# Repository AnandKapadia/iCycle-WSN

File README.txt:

README: 

This repository contains all of the files and documentation for the iCycle project. 

00_Documentation
01_Hardware 
	01_00_Reference
		Sparkfun library for the ATmega128RFA1_Dev (https://github.com/sparkfun/ATmega128RFA1_Dev)
	01_01_Library
	01_02_PCB
		v0.1 with arduinio mini, not finished, needs 4 layers
		v0.2 completed board with xbee, buzzer, leds
02_Software 
	01_00_Reference
		Sparkfun library for the ATmega128RFA1_Dev (https://github.com/sparkfun/ATmega128RFA1_Dev)

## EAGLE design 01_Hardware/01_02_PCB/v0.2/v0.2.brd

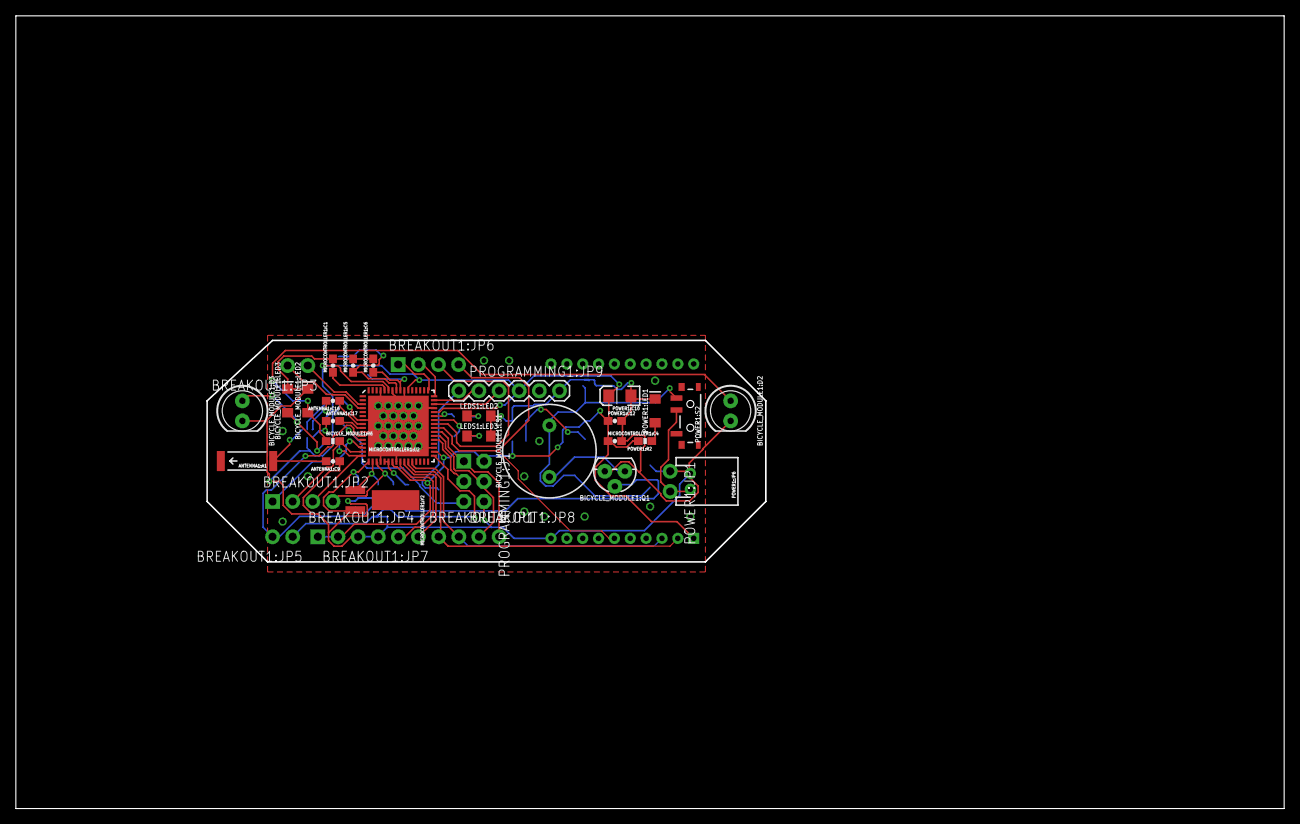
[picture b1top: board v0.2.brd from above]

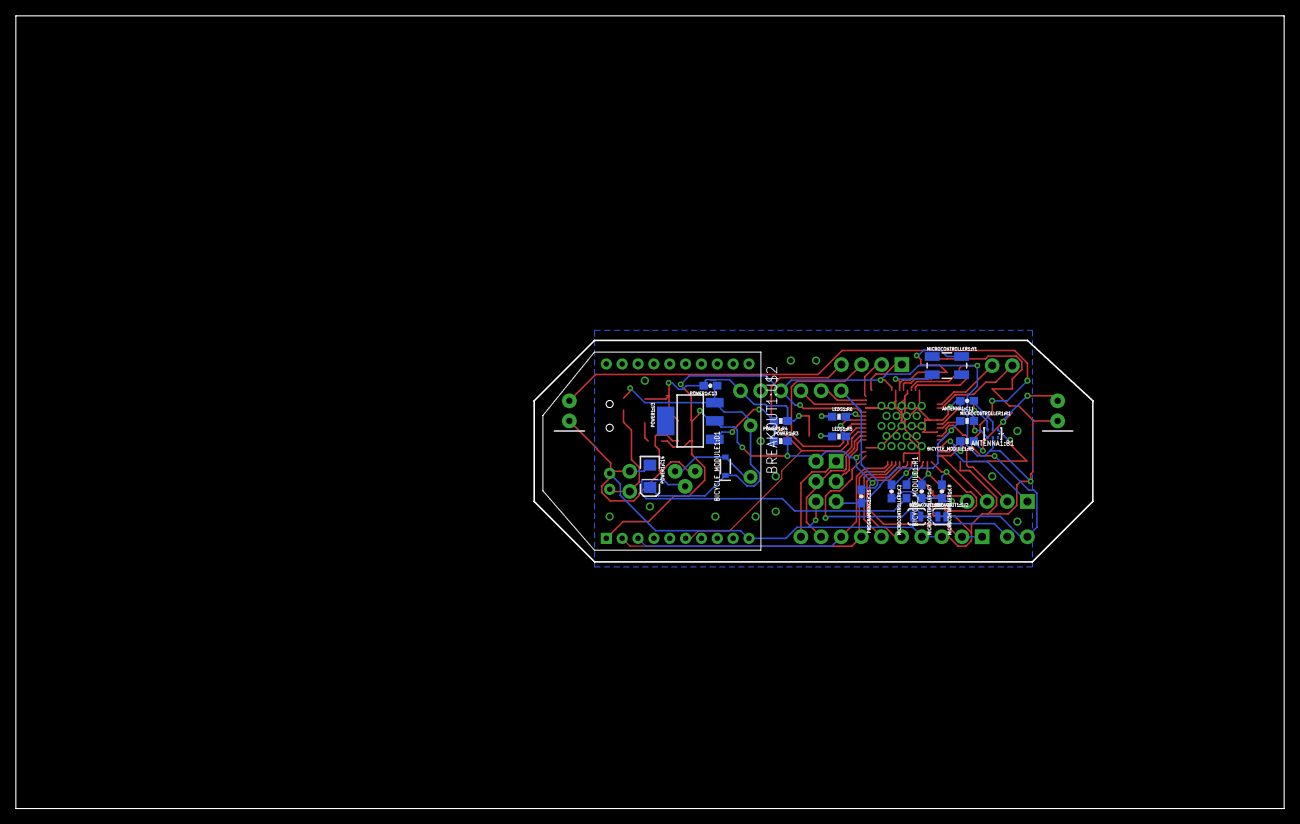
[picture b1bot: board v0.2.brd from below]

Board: 2 copper layers, 160.0 x 100.0 mm, 57 parts (21 on the bottom side), 49 nets.

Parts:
ANTENNA1:A1: ANTENNA2SMD5; ANTENNA-CHIP5
ANTENNA1:B1: 748421245; BALUN-0805
ANTENNA1:C9: 0.75pF; 0603-CAP
ANTENNA1:C11: 22pF; 0603-CAP
ANTENNA1:C16, ANTENNA1:C17: JUMP; 0603-CAP
BICYCLE_MODULE1:D1: 250mA/100V; SOD-323
BICYCLE_MODULE1:D2, BICYCLE_MODULE1:D3: LED_5MM
BICYCLE_MODULE1:LED2, BICYCLE_MODULE1:LED3: GREEN; LED-1206
BICYCLE_MODULE1:LS1: BUZZER-PTH; BUZZER-12MM
BICYCLE_MODULE1:Q1: 600mA/40V; TO-92
BICYCLE_MODULE1:R1: 180; 0603
BICYCLE_MODULE1:R5, BICYCLE_MODULE1:R6: 330; 0603-RES
BREAKOUT1:JP1, BREAKOUT1:JP3, BREAKOUT1:JP5, BREAKOUT1:JP7, BREAKOUT1:JP8: 1X02_NO_SILK
BREAKOUT1:JP2, BREAKOUT1:JP4, BREAKOUT1:JP6: 1X04_NO_SILK
BREAKOUT1:SJ1, BREAKOUT1:SJ2: SJ_2S-TRACE
BREAKOUT1:U$2: XBEE
LEDS1:LED2, LEDS1:LED3: GREEN; LED-1206
LEDS1:R5, LEDS1:R6: 330; 0603-RES
MICROCONTROLLER1:C1, MICROCONTROLLER1:C2, MICROCONTROLLER1:C4: 1uF; 0603-CAP
MICROCONTROLLER1:C5, MICROCONTROLLER1:C6, MICROCONTROLLER1:C7, MICROCONTROLLER1:C8: 12pF; 0603-CAP
MICROCONTROLLER1:R1: 10k; 0603-RES
MICROCONTROLLER1:U2: ATMEGA128RFA1; QFN-64
MICROCONTROLLER1:Y1: 16MHz; CRYSTAL-SMD-5X3
MICROCONTROLLER1:Y2: 32.768kHz; CRYSTAL-32KHZ-SMD
POWER1:C10, POWER1:C14: 10uF; EIA3216
POWER1:C12: 1uF; 0603-CAP
POWER1:C13: 0.1uF; 0603-CAP
POWER1:JP1: 1X02_NO_SILK
POWER1:JP6: JST-2-PTH
POWER1:LED1: RED; LED-1206
POWER1:R2: 1k; 0603-RES
POWER1:R3: 240; 0603-RES
POWER1:R4: 390; 0603-RES
POWER1:S2: SWITCH-SPST-SMD-A
POWER1:U3: LM1117; SOT223
PROGRAMMING1:C15: 0.1uF; 0603-CAP
PROGRAMMING1:J1: ISP; 2X3-NS
PROGRAMMING1:JP9: FTDI; FTDI_BASIC

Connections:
3.3V: BREAKOUT1:JP4.1, BREAKOUT1:JP4.2, BREAKOUT1:U$2.1, MICROCONTROLLER1:C4.1, MICROCONTROLLER1:R1.2, MICROCONTROLLER1:U2.23, MICROCONTROLLER1:U2.34, MICROCONTROLLER1:U2.44, MICROCONTROLLER1:U2.54, MICROCONTROLLER1:U2.59, POWER1:C10.A, POWER1:C12.1, POWER1:R2.2, POWER1:R3.2, POWER1:U3.2, PROGRAMMING1:J1.2, PROGRAMMING1:JP9.VCC
A4: BREAKOUT1:JP3.1, MICROCONTROLLER1:U2.3
A5: BREAKOUT1:JP3.2, MICROCONTROLLER1:U2.4
ANTENNA1:N$62: ANTENNA1:B1.2, ANTENNA1:C11.1
ANTENNA1:N$63: ANTENNA1:B1.3, ANTENNA1:C16.2
ANTENNA1:N$64: ANTENNA1:B1.4, ANTENNA1:C17.1
ANTENNA1:RFANT: ANTENNA1:A1.FEED, ANTENNA1:B1.1, ANTENNA1:C9.2
AVDD: MICROCONTROLLER1:C1.1, MICROCONTROLLER1:U2.60
BICYCLE_MODULE1:N$1: BICYCLE_MODULE1:Q1.2, BICYCLE_MODULE1:R1.2
BICYCLE_MODULE1:N$2: BICYCLE_MODULE1:D1.A, BICYCLE_MODULE1:LS1.-, BICYCLE_MODULE1:Q1.1
BICYCLE_MODULE1:N$65: BICYCLE_MODULE1:D3.A, BICYCLE_MODULE1:LED3.A, BICYCLE_MODULE1:R5.1
BICYCLE_MODULE1:N$66: BICYCLE_MODULE1:D2.A, BICYCLE_MODULE1:LED2.A, BICYCLE_MODULE1:R6.1
CLKI: BREAKOUT1:JP5.1, BREAKOUT1:SJ1.2, MICROCONTROLLER1:U2.33
DVDD: MICROCONTROLLER1:C2.1, MICROCONTROLLER1:U2.21, MICROCONTROLLER1:U2.22
GND: ANTENNA1:B1.5, ANTENNA1:C9.1, ANTENNA1:C11.2, BICYCLE_MODULE1:D2.K, BICYCLE_MODULE1:D3.K, BICYCLE_MODULE1:LED2.C, BICYCLE_MODULE1:LED3.C, BICYCLE_MODULE1:Q1.3, BREAKOUT1:JP4.3, BREAKOUT1:JP4.4, BREAKOUT1:SJ1.1, BREAKOUT1:SJ2.1, BREAKOUT1:U$2.10, LEDS1:LED2.C, LEDS1:LED3.C, MICROCONTROLLER1:C1.2, MICROCONTROLLER1:C2.2, MICROCONTROLLER1:C4.2, MICROCONTROLLER1:C5.2, MICROCONTROLLER1:C6.2, MICROCONTROLLER1:C7.2, MICROCONTROLLER1:C8.2, MICROCONTROLLER1:U2.7, MICROCONTROLLER1:U2.10, MICROCONTROLLER1:U2.20, MICROCONTROLLER1:U2.24, MICROCONTROLLER1:U2.35, MICROCONTROLLER1:U2.45, MICROCONTROLLER1:U2.55, MICROCONTROLLER1:U2.58, MICROCONTROLLER1:U2.61, MICROCONTROLLER1:U2.65, POWER1:C10.C, POWER1:C12.2, POWER1:C13.2, POWER1:C14.C, POWER1:JP1.1, POWER1:JP6.1, POWER1:LED1.C, POWER1:R4.1, PROGRAMMING1:J1.6, PROGRAMMING1:JP9.GND
LEDS1:N$65: LEDS1:LED3.A, LEDS1:R5.1
LEDS1:N$66: LEDS1:LED2.A, LEDS1:R6.1
MICROCONTROLLER1:N$57: MICROCONTROLLER1:C5.1, MICROCONTROLLER1:U2.57, MICROCONTROLLER1:Y1.3
MICROCONTROLLER1:N$58: MICROCONTROLLER1:C6.1, MICROCONTROLLER1:U2.56, MICROCONTROLLER1:Y1.1
MICROCONTROLLER1:N$59: MICROCONTROLLER1:C7.1, MICROCONTROLLER1:U2.18, MICROCONTROLLER1:Y2.X1
MICROCONTROLLER1:N$60: MICROCONTROLLER1:C8.1, MICROCONTROLLER1:U2.17, MICROCONTROLLER1:Y2.X2
MISO: BREAKOUT1:JP8.2, MICROCONTROLLER1:U2.39, PROGRAMMING1:J1.1
MOSI: BREAKOUT1:JP8.1, MICROCONTROLLER1:U2.38, PROGRAMMING1:J1.4
PB4: BREAKOUT1:JP6.4, BREAKOUT1:U$2.6, MICROCONTROLLER1:U2.40
PB5: BREAKOUT1:JP6.3, MICROCONTROLLER1:U2.41
PB6: LEDS1:R5.2, MICROCONTROLLER1:U2.42
PB7: LEDS1:R6.2, MICROCONTROLLER1:U2.43
PE2: BREAKOUT1:JP6.2, MICROCONTROLLER1:U2.48
PE3: BREAKOUT1:JP6.1, MICROCONTROLLER1:U2.49
PG0: BREAKOUT1:JP2.1, MICROCONTROLLER1:U2.14
PG1: BICYCLE_MODULE1:R6.2, BREAKOUT1:JP2.2, MICROCONTROLLER1:U2.15
PG2: BICYCLE_MODULE1:R5.2, BREAKOUT1:JP2.3, MICROCONTROLLER1:U2.16
PG5: BICYCLE_MODULE1:R1.1, BREAKOUT1:JP2.4, MICROCONTROLLER1:U2.19
POWER1:FB: POWER1:R3.1, POWER1:R4.2, POWER1:U3.1
POWER1:N$61: POWER1:LED1.A, POWER1:R2.1
POWER1:N$67: POWER1:JP1.2, POWER1:JP6.2, POWER1:S2.2
PROGRAMMING1:DTR: PROGRAMMING1:C15.1, PROGRAMMING1:JP9.DTR
RESET: MICROCONTROLLER1:R1.1, MICROCONTROLLER1:U2.12, PROGRAMMING1:C15.2, PROGRAMMING1:J1.5
RFN: ANTENNA1:C17.2, MICROCONTROLLER1:U2.9
RFP: ANTENNA1:C16.1, MICROCONTROLLER1:U2.8
RX0: MICROCONTROLLER1:U2.46, PROGRAMMING1:JP9.TXO
RX1: BREAKOUT1:JP1.1, BREAKOUT1:U$2.2, MICROCONTROLLER1:U2.27
SCK: MICROCONTROLLER1:U2.37, PROGRAMMING1:J1.3
SCL: BREAKOUT1:JP7.2, MICROCONTROLLER1:U2.25
SDA: BREAKOUT1:JP7.1, MICROCONTROLLER1:U2.26
TST: BREAKOUT1:JP5.2, BREAKOUT1:SJ2.2, MICROCONTROLLER1:U2.11
TX0: MICROCONTROLLER1:U2.47, PROGRAMMING1:JP9.RXI
TX1: BREAKOUT1:JP1.2, BREAKOUT1:U$2.3, MICROCONTROLLER1:U2.28
VCC: BICYCLE_MODULE1:D1.C, BICYCLE_MODULE1:LS1.+, POWER1:C13.1, POWER1:C14.A, POWER1:S2.1, POWER1:U3.3

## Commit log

2018-03-29 Init
    repo setup
2018-03-29 eagle repo setup
2018-03-30 adding board v0.1, v0.2 to version control
2018-03-30 v0.2 updates (minor traces), readme updates
2018-04-02 xbee library and basic arduino code
2018-04-04 Arduino XBee: Mid-demo nodes
    New Arduino project for each the bike, corner and master node using
    series 1 XBees in API mode. Bike sends a broadcast, two corners
    receive and send the RSSI from the broadcast to the master, along with
    the nodeID of the bike node. Plenty to clean up, but the master seems to
    be deciding the binary location of the bike fairly well based on the
    RSSI from the two corners.
2018-04-04 Initial commit for master node code
2018-04-04 Added feature to display vehicle
2018-04-04 Correctly displays car on white background
2018-04-04 Added bicycle image
2018-04-04 Display bicycle in each direction
2018-04-04 Moved display to separate module
2018-04-05 Renders bicycle in given direction
2018-04-05 added library for accelerometer
2018-04-05 Master: support for multiple bikes and master as corner
2018-04-05 added imu support in bicycle node
2018-04-05 Added xbee drivers for writing and receiving
2018-04-05 Master with buzzer debugging
2018-04-05 bike node now reads from master
2018-04-05 Added write from master to bicycle
2018-04-09 Corner Node: added bike payload bytes for IMU data
2018-04-29 3v3 reg uptE
2018-04-29 Creating AS project for Mole rx/tx
2018-04-30 Corner Mole: sending periodically and receiving payload
2018-04-30 Corner Mole: refactored rx/tx into a seperate file, added common message structs
2018-04-30 Bike Mole: Initialize Project
    First cde for bike mole. Currenlty sends a message with four payload
    bytes at a fixed rate. Receives messages, but does not process them yet
    Corner with bike, and attempted to retransmit bike message to the
    master. Bike lights/buzzer and IMU yet to be implemented.
2018-04-30 WIP: Moved xbee files to uart, created corner pthread
2018-05-01 Bike Mole: Added IO response on reception
    When the bike mole receives a packet from the master, it now reads its
    relative location and sets the appropriate LEDs for the vehicles
    location. A timer is started at the expiry of which the LEDs are turned
    off. Buzzer code is commented out as the buzzer is not yet attached to
    the hardware.
2018-05-01 Corner Mole: add cproj
2018-05-01 Corner Mole: Add Serial
2018-05-01 Corner Mole: added RSSI printout upon reception of bike message
2018-05-01 Corner and Bike: increasing tx power and switching channel
2018-05-01 WIP: Modifying serial for master mole
2018-05-01 Master Mole: Initialize project
2018-05-01 WIP: Created additional directory for managing header files
2018-05-01 msg_structs.h: Moved to general Includes directory
2018-05-01 Includes: integrate header definitions
2018-05-01 WIP: integrating uart.h file
2018-05-01 Master Mole: receive wireless packets and transfer to pi
    Master receives packets from corner nodes and bicycle node. Based on
    this distinction, the master parses the message and transfers the
    information via uart to the pi master. Receiving from the pi has yet to
    be implemented.
2018-05-01 Corner Mole: Enable transmission to master
2018-05-01 Master Mole: Change mole ID and pi packet
2018-05-01 Corner Mole: Add delay to avoid collisions
    After recpetion of a pack, the node now delays an extra amount of time
    based on its address, such that all nodes will send at different offsets
    after bike message reception. With two nodes this seems good enough for
    collision avoidance.
2018-05-01 WIP: debugging packet length detaiils
2018-05-01 WIP: debugging segfault
2018-05-02 Master: receive uart packet from pi master
2018-05-02 Bike and Master: minor fixes
2018-05-02 Moles: parameterize txrx blink speed
2018-05-02 Works with four nodes, added freshness

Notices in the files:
parts and their libraries:
SparkFun-RF: Licensing: CC v3.0 Share-Alike You are welcome to use this library for commercial purposes.
SparkFun-DiscreteSemi: Licensing: Creative Commons ShareAlike 4.0 International - https://creativecommons.org/licenses/by-sa/4.0
